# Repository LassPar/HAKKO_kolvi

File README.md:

# HAKKO_kolvi
PID-ohjattu kolvi

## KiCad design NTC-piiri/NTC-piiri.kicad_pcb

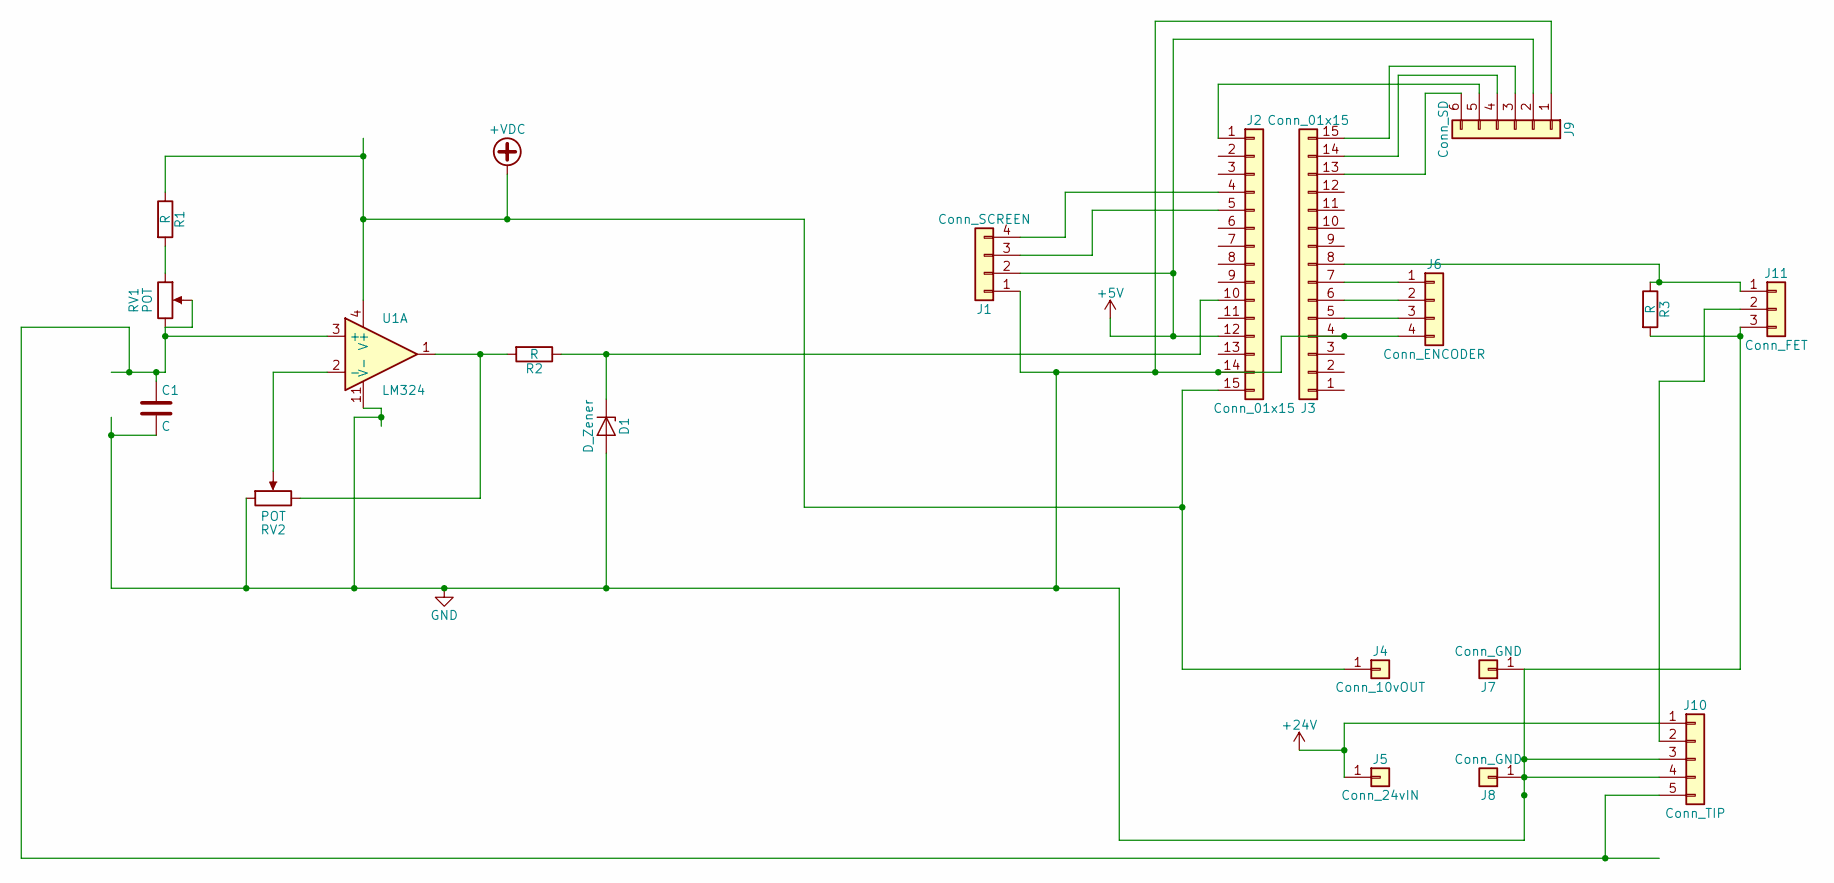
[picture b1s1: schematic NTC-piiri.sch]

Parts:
C1: C; C_Disc_D4.3mm_W1.9mm_P5.00mm
D1: D_Zener; D_A-405_P7.62mm_Horizontal
J1: Conn_SCREEN; Socket_Strip_Straight_1x04_Pitch2.54mm
J2, J3: Conn_01x15; Socket_Strip_Straight_1x15_Pitch2.54mm
J4: Conn_10vOUT; Socket_Strip_Straight_1x01_Pitch2.54mm
J5: Conn_24vIN; Socket_Strip_Straight_1x01_Pitch2.54mm
J6: Conn_ENCODER; Socket_Strip_Straight_1x04_Pitch2.54mm
J7, J8: Conn_GND; Socket_Strip_Straight_1x01_Pitch2.54mm
J9: Conn_SD; Socket_Strip_Straight_1x06_Pitch2.54mm
J10: Conn_TIP; Socket_Strip_Straight_1x05_Pitch2.54mm
J11: Conn_FET; Socket_Strip_Straight_1x03_Pitch2.54mm
R1, R2, R3: R; R_Axial_DIN0207_L6.3mm_D2.5mm_P7.62mm_Horizontal
RV1, RV2: POT; Potentiometer_Trimmer_Bourns_3296W
U1: LM324; DIP-14_W7.62mm

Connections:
+5V: J1.2, J2.12, J9.2
+24V: J5.1, J10.1
+VDC: J2.15, J4.1, R1.1, U1.4 (V+)
GND: C1.2, D1.2 (A), J1.1, J2.14, J3.4, J6.4, J7.1, J8.1, J9.1, J10.3, J10.4, J11.3, R3.2, RV2.1, U1.11 (V-)
unnamed: C1.1, J10.5, RV1.2, RV1.3, U1.3 (+)
unnamed: D1.1 (K), J2.10, R2.1
unnamed: J1.3, J2.5
unnamed: J1.4, J2.4
unnamed: J2.1, J9.5
unnamed: J3.5, J6.3
unnamed: J3.6, J6.2
unnamed: J3.7, J6.1
unnamed: J3.13, J9.6
unnamed: J3.14, J9.4
unnamed: J3.15, J9.3
unnamed: J10.2, J11.2
unnamed: J3.8, J11.1, R3.1
unnamed: R1.2, RV1.1
unnamed: R2.2, RV2.3, U1.1
unnamed: RV2.2, U1.2 (-)

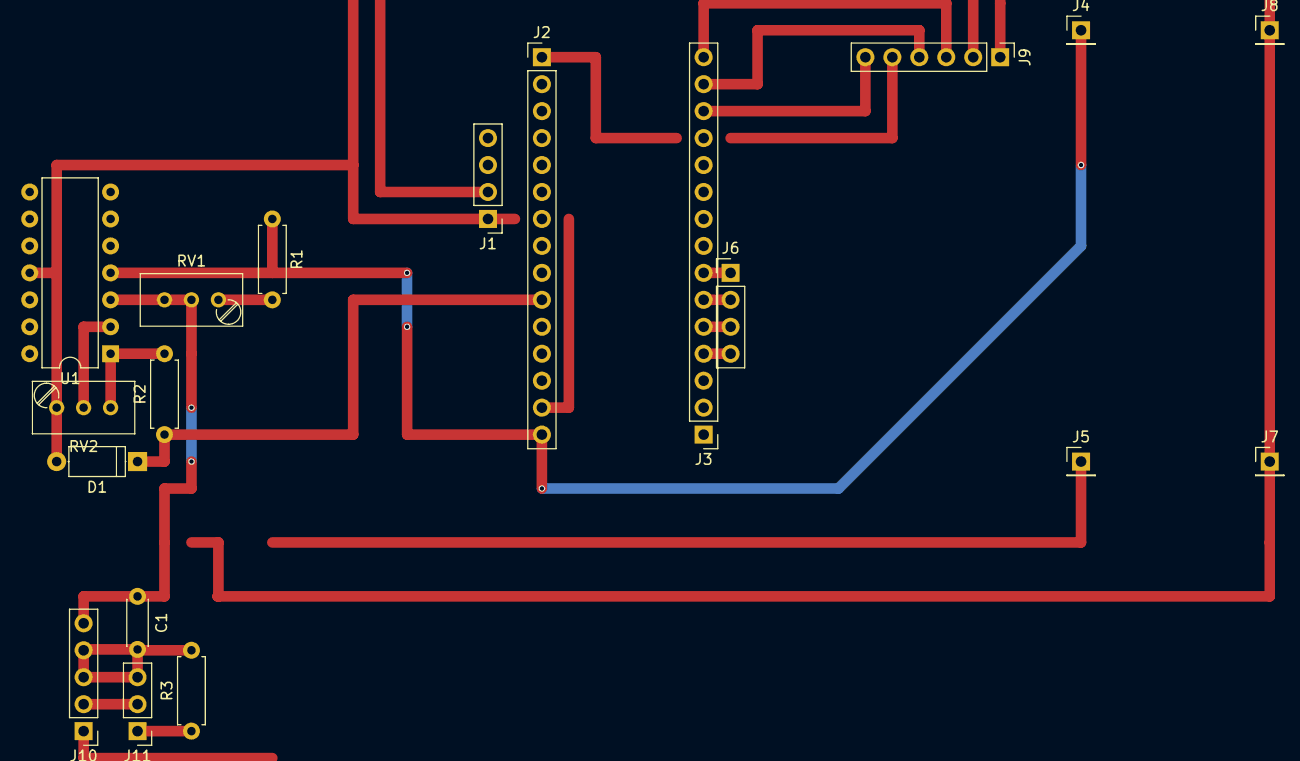
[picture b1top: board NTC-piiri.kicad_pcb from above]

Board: 2 copper layers, 19 parts (0 on the bottom side), 20 nets.

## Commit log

2019-02-07 Lisätty valmis projekti
2019-02-07 turhaa
